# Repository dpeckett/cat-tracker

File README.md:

# Cat Tracker

An active RFID system for locating free roaming pets / wildlife. Uses a compact handheld radio direction finding receiver rather than GPS (due to power budget and the need for real-time updates). Kind of a modern take on a traditional wildlife tracker.

## Backstory

My wife and I adopted a free roaming snow bengal cat from a former neighbor. She's a very naughty cat and often decides she wants to spend extended time away from us in the giant wooded park next door.

I've spent many a late night walking in the woods with a kibble bag trying to get her to come home for dinner. I can usually locate her but it's a gigantic PITA.

It would be nice to have a real time GPS position but the commercial tracking collars are bulky (she's a tiny cat), expensive (ongoing fees), and have limited battery life. Of course there is the air tag and tile products, which I think are probably amazing in an urban area but our cat is often found in the dense woods far away from other people.

None of the existing solutions satisfied me so I decided to build my own. It had to be very compact, have a long battery life (months or years), and no ongoing costs.

## Notes

### Edit the Radio Configuration For Your Region

If you are outside the EU you will probably need to modify the radio configuration in [firmware/CatTracker/Base/subghz_radio.h](./firmware/CatTracker/Base/subghz_radio.h) to match your legislative region.

### To Unlock A STM32WLExx

Telnet into the OpenOCD server:

```
telnet localhost 4444
```

And run the following commands:

```
stm32l4x unlock 0
# Clear FLASH_OPTR
stm32l4x option_write 0 0x20 0xbffff0aa
# Power cycle the device
halt
stm32l4x mass_erase 0
```

### To Read The Unique ID From A STM32WLExx

Telnet into the OpenOCD server:

```
telnet localhost 4444
```

And run the following commands:

```
mdw 0x1FFF7590
```

## Errata

### EBYTE E77-900M22S Dev Boards

My boards arrived with a capacitor missing from the lowpass filter before the SMA jack. This meant the antenna jack was completely disconnected.

### PCB

The footprint for the battery holder needs a larger keep out area so that the center pad makes good contact. I temporarily resolved this by raising the pad with some additional solder.

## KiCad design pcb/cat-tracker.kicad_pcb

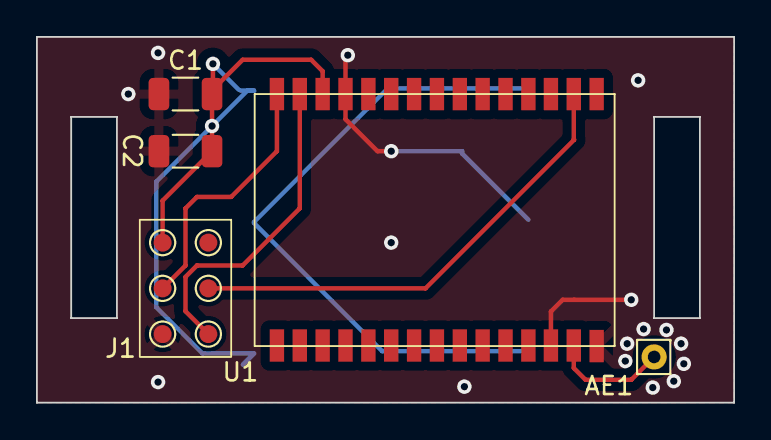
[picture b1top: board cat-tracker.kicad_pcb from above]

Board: 2 copper layers, 38.7 x 20.3 mm, 5 parts (0 on the bottom side), 6 nets.

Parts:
AE1: Antenna; Pin_D0.7mm_L6.5mm_W1.8mm_FlatFork
C1: 1uF; C_1206_3216Metric
C2: 10uF; C_1206_3216Metric
J1: SWD
U1: E07-900M10S

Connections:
GND: C1.2, C2.2, J1.3, U1.13 (GND), U1.15 (GND), U1.27 (GND)
unnamed: AE1.1 (A), U1.14 (ANT)
unnamed: J1.2, U1.30 (SWCLK)
unnamed: J1.4, U1.29 (SWDIO)
unnamed: J1.5, U1.17 (NRST)
VDD: C1.1, C2.1, J1.1, U1.28 (VDD)

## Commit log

2023-07-21 feat: Initial public release
2023-07-22 feat: Include a modelling shot
